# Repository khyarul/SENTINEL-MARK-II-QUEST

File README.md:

# SENTINEL MARK II (QUEST) - Line Follower Path Planning + Oled I2C User Interface
- Arduino compatible based on Maple Mini board (STM32F103CBT6)
- Burn and update firmware via USB-OTG
- BTS7960 motor driver 2 port + encoder
- OLED I2C SSD1306 128x64
- external eeprom (24LCxxx)
- 2 port for mini servo 5V
- 1 port for extinguisher motor (adjustable voltage using PWM) 
- external serial port (Serial1)

### Schematic (made using Kicad)
available in "Schematic" folder:
- SENTINEL Mark II - Quest.pro (Kicad Project)

### Gerber (3 board):
- Core + Driver motor: [Here](https://www.pcbway.com/project/shareproject/SENTINEL_mark_II__QUEST___Core___motor_driver_.html)
- Button + LCD: [Here](https://www.pcbway.com/project/shareproject/SENTINEL_mark_II__QUEST___button___eeprom___lcd_.html)
- Sensor: [Here](https://www.pcbway.com/project/shareproject/SENTINEL_mark_II__QUEST___Sensor_.html)

### Board Preview

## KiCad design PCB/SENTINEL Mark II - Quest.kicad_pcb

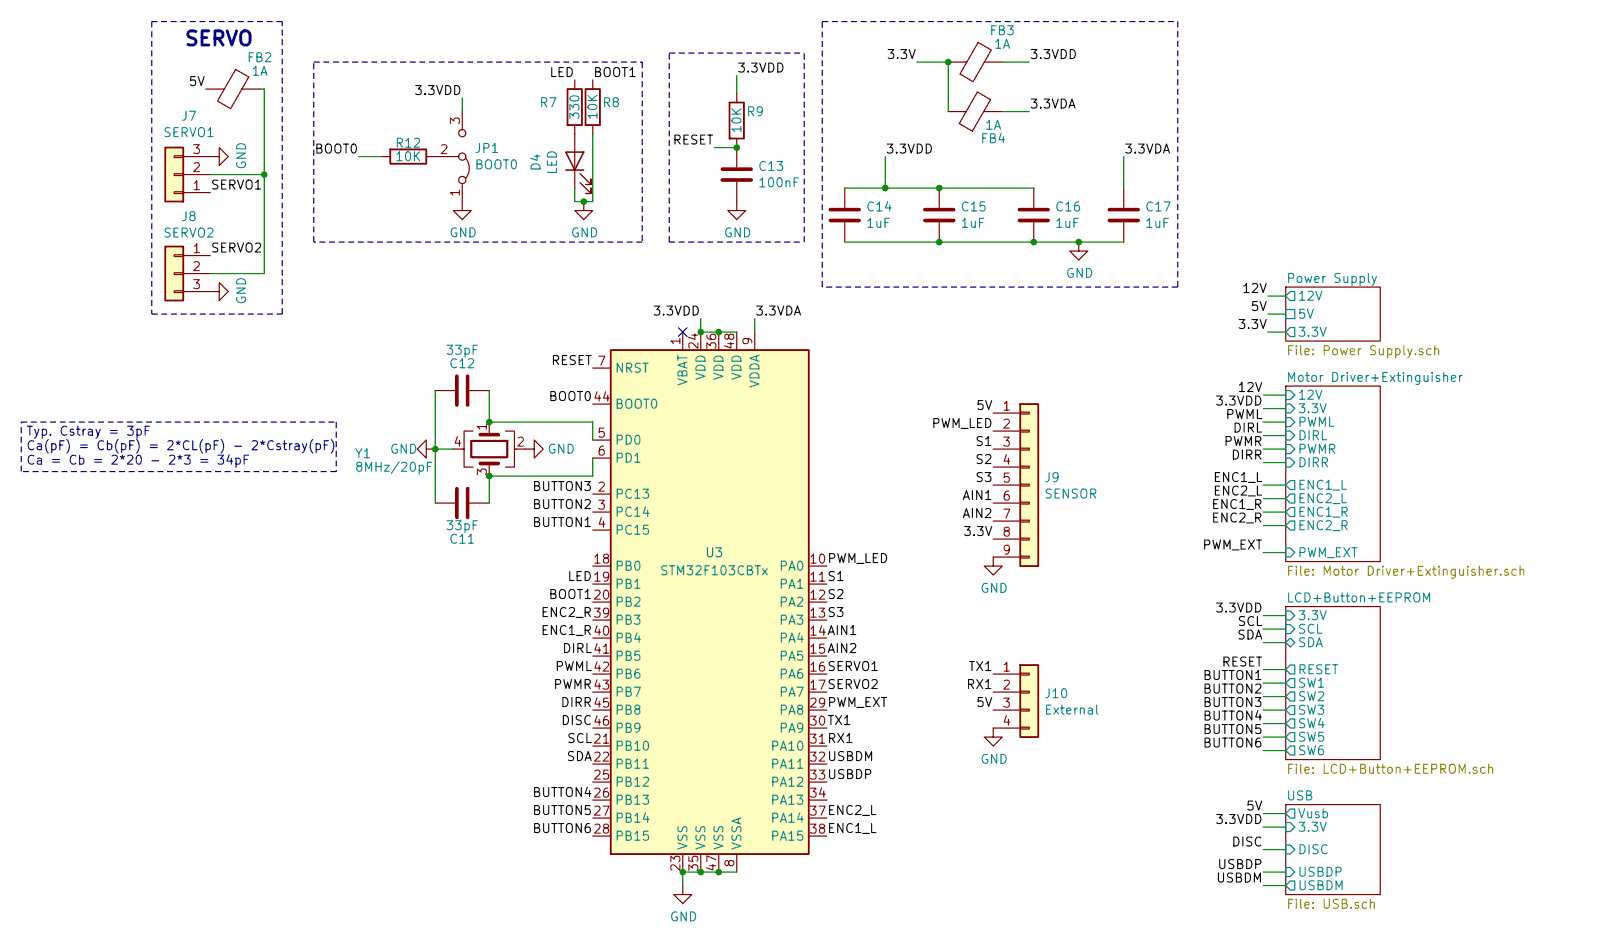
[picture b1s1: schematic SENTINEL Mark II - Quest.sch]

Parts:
C11, C12: 33pF; C_0805_2012Metric
C13: 100nF; C_0805_2012Metric
C14, C15, C16, C17: 1uF; C_0805_2012Metric
D4: LED; LED_0805_2012Metric
FB2, FB3, FB4: 1A; L_0805_2012Metric
J7: SERVO1; PinHeader_1x03_P2.54mm_Vertical
J8: SERVO2; PinHeader_1x03_P2.54mm_Vertical
J9: SENSOR; PinHeader_1x09_P2.54mm_Horizontal
J10: External; PinHeader_1x04_P2.54mm_Vertical
JP1: BOOT0; PinHeader_1x03_P2.54mm_Vertical
R7: 330; R_0805_2012Metric
R8, R9, R12: 10K; R_0805_2012Metric
U3: STM32F103CBTx; LQFP-48_7x7mm_P0.5mm
Y1: 8MHz/20pF; Crystal_SMD_3225-4Pin_3.2x2.5mm_HandSoldering

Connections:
/3.3V: FB3.2, FB4.1, J9.8; also elsewhere on the board
/3.3VDA: C17.1, FB4.2, U3.9 (VDDA)
/5V: FB2.2, J9.1, J10.3; also elsewhere on the board
/AIN1: J9.6, U3.14 (PA4)
/AIN2: J9.7, U3.15 (PA5)
/BOOT0: R12.2, U3.44 (BOOT0)
/BOOT1: R8.1, U3.20 (PB2)
/BUTTON1: U3.4 (PC15); also elsewhere on the board
/BUTTON2: U3.3 (PC14); also elsewhere on the board
/BUTTON3: U3.2 (PC13); also elsewhere on the board
/BUTTON4: U3.26 (PB13); also elsewhere on the board
/BUTTON5: U3.27 (PB14); also elsewhere on the board
/BUTTON6: U3.28 (PB15); also elsewhere on the board
/DIRL: U3.41 (PB5); also elsewhere on the board
/DIRR: U3.45 (PB8); also elsewhere on the board
/DISC: U3.46 (PB9); also elsewhere on the board
/ENC1_L: U3.38 (PA15); also elsewhere on the board
/ENC2_L: U3.37 (PA14); also elsewhere on the board
/LED: R7.1, U3.19 (PB1)
/PWML: U3.42 (PB6); also elsewhere on the board
/PWMR: U3.43 (PB7); also elsewhere on the board
/PWM_EXT: U3.29 (PA8); also elsewhere on the board
/PWM_LED: J9.2, U3.10 (PA0)
/RESET: C13.1, R9.2, U3.7 (NRST); also elsewhere on the board
/RX1: J10.2, U3.31 (PA10)
/S1: J9.3, U3.11 (PA1)
/S2: J9.4, U3.12 (PA2)
/S3: J9.5, U3.13 (PA3)
/SCL: U3.21 (PB10); also elsewhere on the board
/SDA: U3.22 (PB11); also elsewhere on the board
/SERVO1: J7.1, U3.16 (PA6)
/SERVO2: J8.1, U3.17 (PA7)
/TX1: J10.1, U3.30 (PA9)
/USBDM: U3.32 (PA11); also elsewhere on the board
/USBDP: U3.33 (PA12); also elsewhere on the board
unnamed: C11.2, U3.6 (PD1), Y1.3
unnamed: C12.2, U3.5 (PD0), Y1.1
unnamed: D4.2 (A), R7.2
unnamed: FB2.1, J7.2, J8.2
unnamed: JP1.2 (C), R12.1

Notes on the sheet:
Typ. Cstray = 3pF Ca(pF) = Cb(pF) = 2*CL(pF) - 2*Cstray(pF) Ca = Cb = 2*20 - 2*3 = 34pF
SERVO

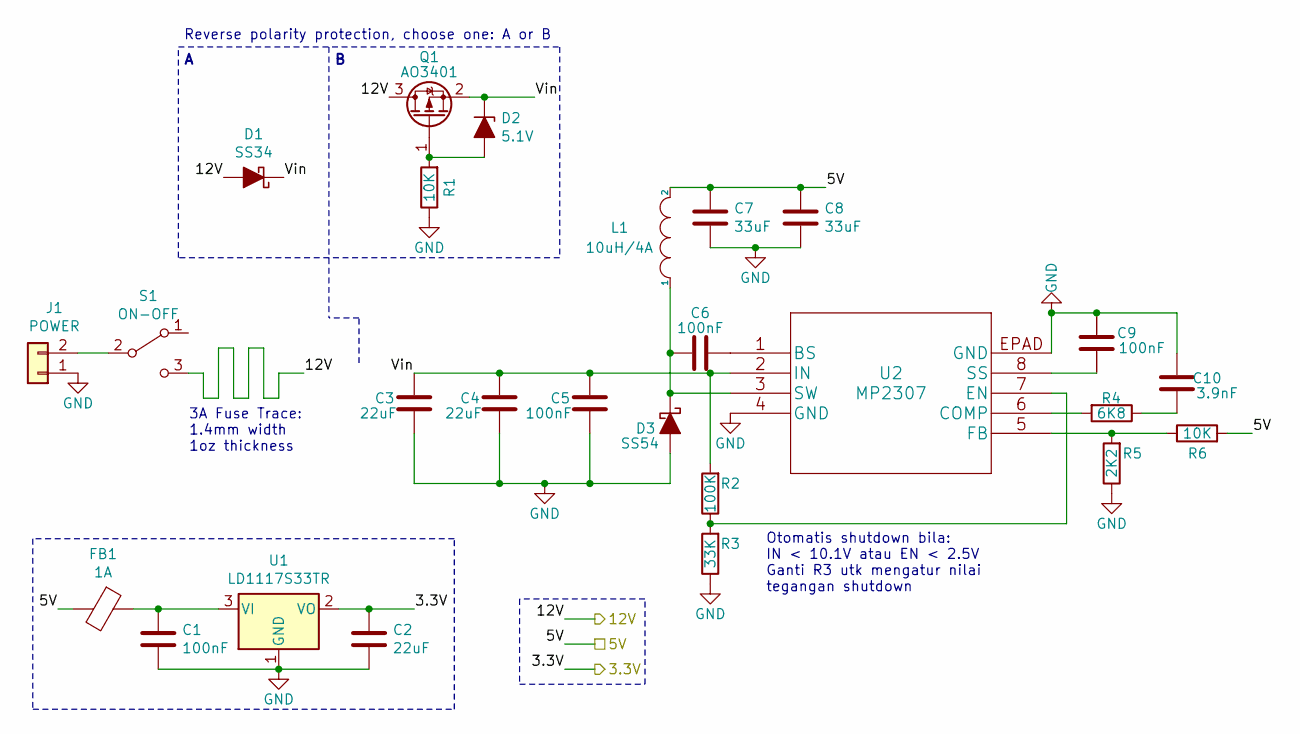
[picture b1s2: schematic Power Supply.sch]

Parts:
C1, C5, C6, C9: 100nF; C_0805_2012Metric
C2, C3, C4: 22uF; C_0805_2012Metric
C7, C8: 33uF; C_0805_2012Metric
C10: 3.9nF; C_0805_2012Metric
D1: SS34; D_SMA
D2: 5.1V; D_SOD-123
D3: SS54; D_SMA
FB1: 1A; L_0805_2012Metric
J1: POWER; PinHeader_1x02_P2.54mm_Vertical
L1: 10uH/4A; L_7.3x7.3_H3.5
Q1: AO3401; SOT-23
R1, R6: 10K; R_0805_2012Metric
R2: 100K; R_0805_2012Metric
R3: 33K; R_0805_2012Metric
R4: 6K8; R_0805_2012Metric
R5: 2K2; R_0805_2012Metric
S1: ON-OFF; switch_slide_2.54
U1: LD1117S33TR; SOT-223-3_TabPin2
U2: MP2307

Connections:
/3.3V: C2.1, U1.2 (VO); also elsewhere on the board
/5V: C7.1, C8.1, FB1.2, L1.2, R6.2; also elsewhere on the board
/12V: D1.2 (A), Q1.3 (D), S1.3 (C); also elsewhere on the board
/Power Supply/Vin: C3.1, C4.1, C5.1, D1.1 (K), D2.1 (K), Q1.2 (S), R2.2, U2.2 (IN)
unnamed: C1.1, FB1.1, U1.3 (VI)
unnamed: C6.1, U2.1 (BS)
unnamed: C6.2, D3.1 (K), L1.1, U2.3 (SW)
unnamed: C9.1, U2.8 (SS)
unnamed: C10.1, R4.1
unnamed: D2.2 (A), Q1.1 (G), R1.2
unnamed: J1.2, S1.2 (B)
unnamed: R2.1, R3.2, U2.7 (EN)
unnamed: R4.2, U2.6 (COMP)
unnamed: R5.2, R6.1, U2.5 (FB)

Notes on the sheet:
Otomatis shutdown bila: IN < 10.1V atau EN < 2.5V Ganti R3 utk mengatur nilai tegangan shutdown
3A Fuse Trace: 1.4mm width 1oz thickness
Reverse polarity protection, choose one: A or B

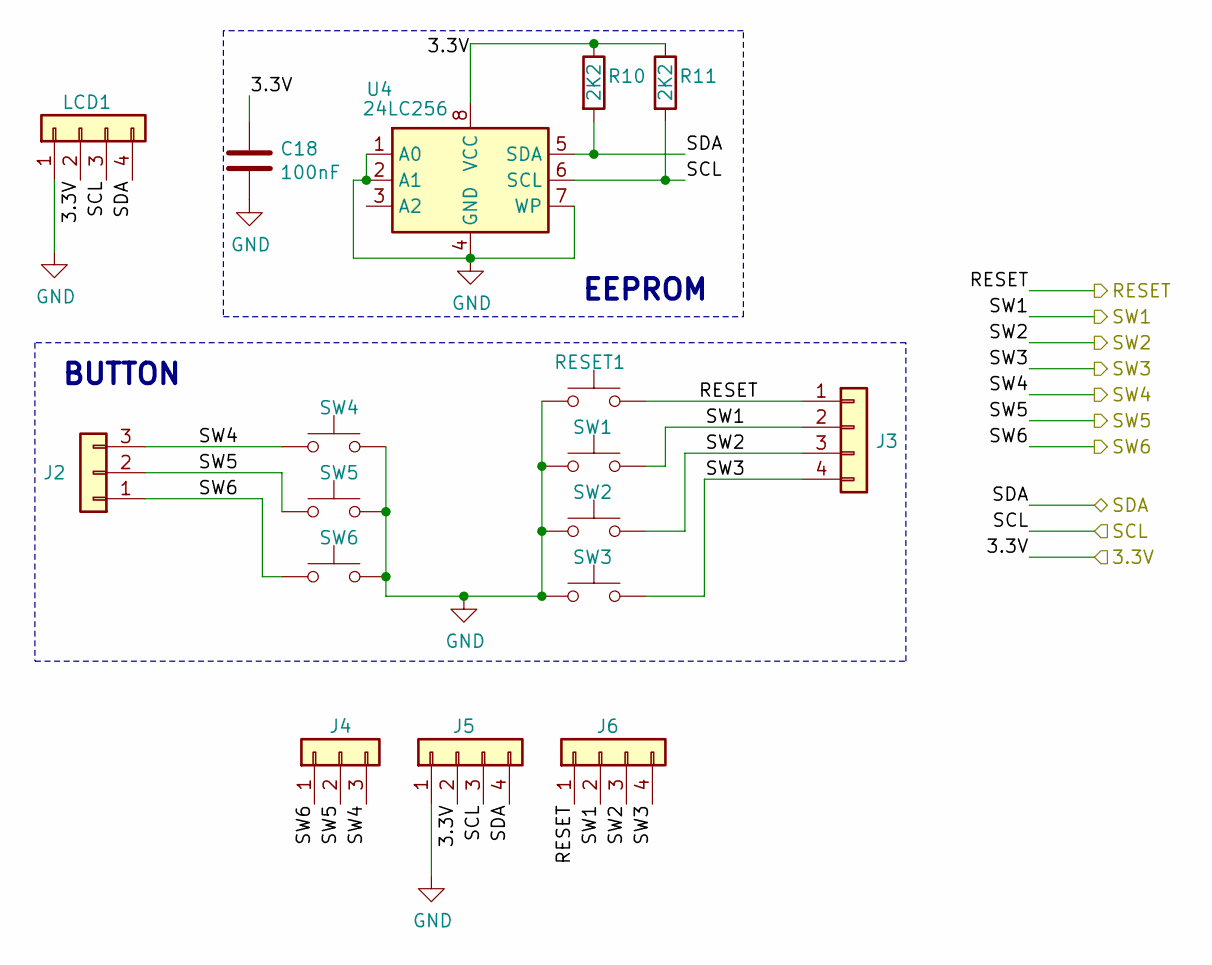
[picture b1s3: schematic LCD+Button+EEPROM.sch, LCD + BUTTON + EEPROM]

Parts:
C18: 100nF; C_0805_2012Metric
J2, J4: Conn_01x03; PinHeader_1x03_P2.54mm_Vertical
J3, J5, J6: Conn_01x04; PinHeader_1x04_P2.54mm_Vertical
LCD1: LCD; OLED_I2C_128x64
R10, R11: 2K2; R_0805_2012Metric
RESET1: RESET; Push_button_silicon_mute
SW1: B1; Push_button_silicon_mute
SW2: B2; Push_button_silicon_mute
SW3: B3; Push_button_silicon_mute
SW4: B4; Push_button_silicon_mute
SW5: B5; Push_button_silicon_mute
SW6: B6; Push_button_silicon_mute
U4: 24LC256; SO-8_3.9x4.9mm_P1.27mm

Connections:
/BUTTON1: J3.2, J6.2, SW1.2; also elsewhere on the board
/BUTTON2: J3.3, J6.3, SW2.2; also elsewhere on the board
/BUTTON3: J3.4, J6.4, SW3.2; also elsewhere on the board
/BUTTON4: J2.3, J4.3, SW4.1; also elsewhere on the board
/BUTTON5: J2.2, J4.2, SW5.1; also elsewhere on the board
/BUTTON6: J2.1, J4.1, SW6.1; also elsewhere on the board
/RESET: J3.1, J6.1, RESET1.2; also elsewhere on the board
/SCL: J5.3, LCD1.3, R11.2, U4.6 (SCL); also elsewhere on the board
/SDA: J5.4, LCD1.4, R10.2, U4.5 (SDA); also elsewhere on the board

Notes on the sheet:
EEPROM
BUTTON

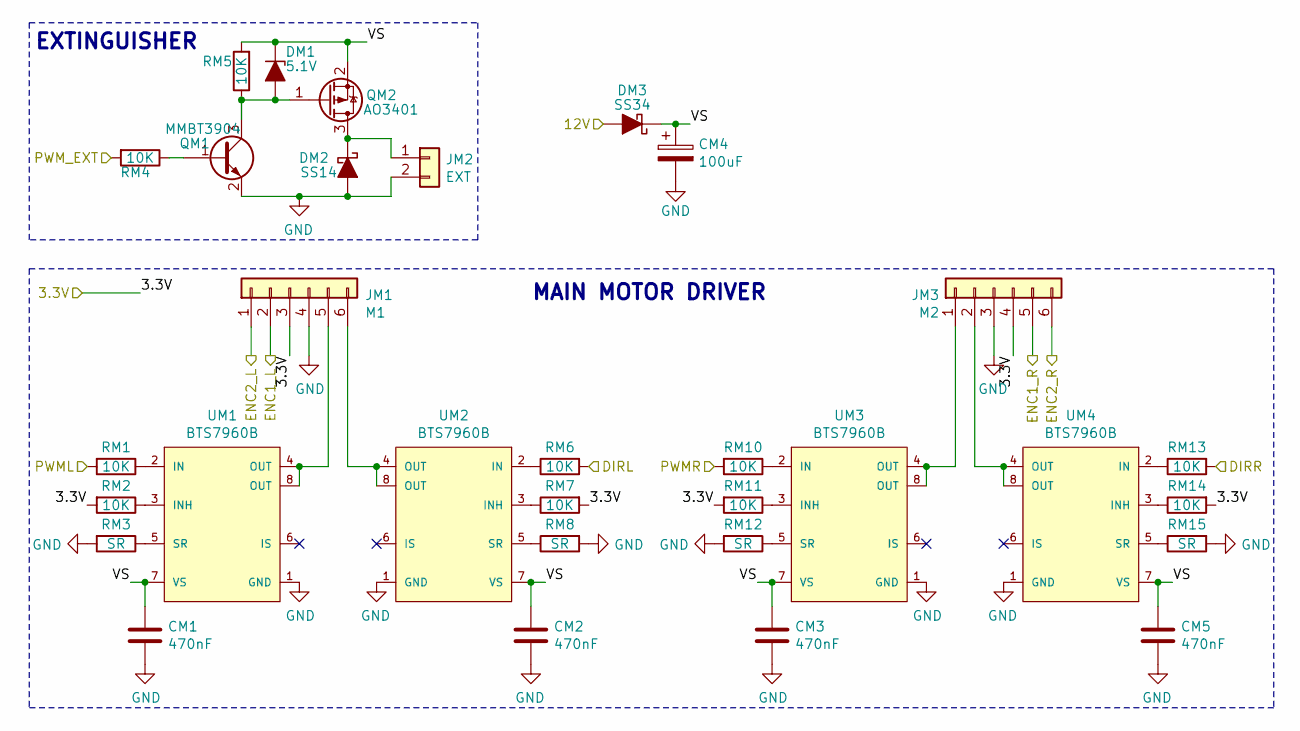
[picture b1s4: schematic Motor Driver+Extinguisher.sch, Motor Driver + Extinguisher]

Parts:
CM1, CM2, CM3, CM5: 470nF; C_0805_2012Metric
CM4: 100uF; CP_Elec_6.3x7.7
DM1: 5.1V; D_SOD-123
DM2: SS14; D_SMA
DM3: SS34; D_SMA
JM1: M1; JST_PH_S6B-PH-K_1x06_P2.00mm_Horizontal
JM2: EXT; PinHeader_1x02_P2.54mm_Vertical
JM3: M2; JST_PH_S6B-PH-K_1x06_P2.00mm_Horizontal
QM1: MMBT3904; SOT-23
QM2: AO3401; SOT-23
RM1, RM2, RM4, RM5, RM6, RM7, RM10, RM11, RM13, RM14: 10K; R_0805_2012Metric
RM3, RM8, RM12, RM15: SR; R_0805_2012Metric
UM1, UM2, UM3, UM4: BTS7960B; Infineon-BTS7960B-Level_A

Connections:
/12V: DM3.2 (A); also elsewhere on the board
/DIRL: RM6.2; also elsewhere on the board
/DIRR: RM13.2; also elsewhere on the board
/ENC1_L: JM1.2; also elsewhere on the board
/ENC2_L: JM1.1; also elsewhere on the board
/Motor Driver+Extinguisher/VS: CM1.1, CM2.1, CM3.1, CM4.1, CM5.1, DM1.1 (K), DM3.1 (K), QM2.2 (S), RM5.2, UM1.7 (VS), UM2.7 (VS), UM3.7 (VS), UM4.7 (VS); also elsewhere on the board
/PWML: RM1.2; also elsewhere on the board
/PWMR: RM10.2; also elsewhere on the board
/PWM_EXT: RM4.2; also elsewhere on the board
unnamed: DM1.2 (A), QM1.3 (C), QM2.1 (G), RM5.1
unnamed: DM2.1 (K), JM2.1, QM2.3 (D)
unnamed: JM1.5, UM1.4 (OUT), UM1.8 (OUT)
unnamed: JM1.6, UM2.4 (OUT), UM2.8 (OUT)
unnamed: QM1.1 (B), RM4.1
unnamed: RM1.1, UM1.2 (IN)
unnamed: RM2.1, UM1.3 (INH)
unnamed: RM3.1, UM1.5 (SR)
unnamed: RM6.1, UM2.2 (IN)
unnamed: RM7.1, UM2.3 (INH)
unnamed: RM8.1, UM2.5 (SR)
unnamed: RM10.1, UM3.2 (IN)
unnamed: RM11.1, UM3.3 (INH)
unnamed: RM12.1, UM3.5 (SR)
unnamed: RM13.1, UM4.2 (IN)
unnamed: RM14.1, UM4.3 (INH)
unnamed: RM15.1, UM4.5 (SR)

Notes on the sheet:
MAIN MOTOR DRIVER
EXTINGUISHER

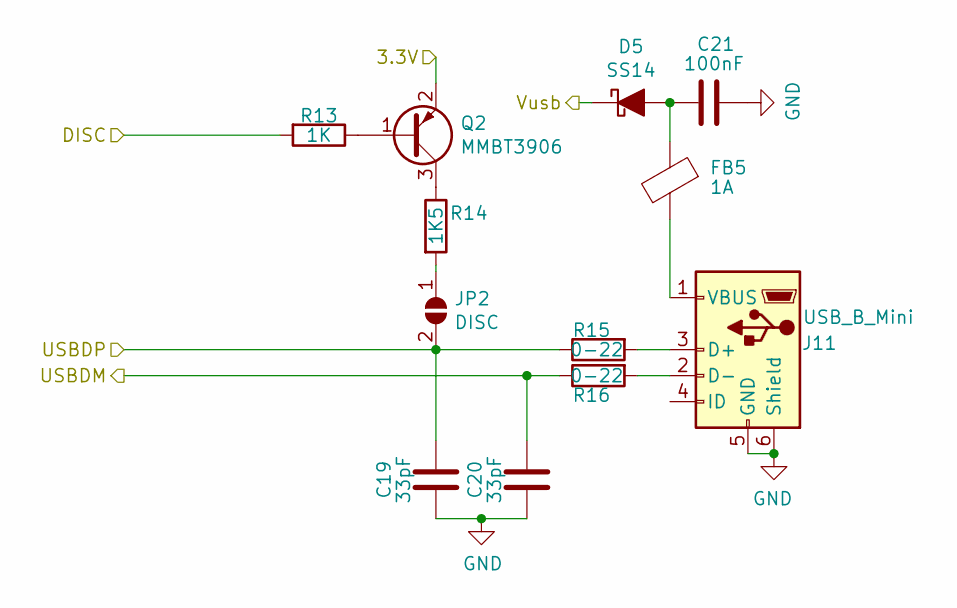
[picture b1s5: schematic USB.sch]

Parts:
C19, C20: 33pF
C21: 100nF
D5: SS14
FB5: 1A
J11: USB_B_Mini
JP2: DISC
Q2: MMBT3906; SOT-23
R13: 1K
R14: 1K5
R15, R16: 0-22

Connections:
/5V: D5.1 (K); also elsewhere on the board
/DISC: R13.2; also elsewhere on the board
/USBDM: C20.1, R16.1; also elsewhere on the board
/USBDP: C19.1, JP2.2 (B), R15.1; also elsewhere on the board
unnamed: C21.2, D5.2 (A), FB5.1
unnamed: FB5.2, J11.1 (VBUS)
unnamed: J11.2 (D-), R16.2
unnamed: J11.3 (D+), R15.2
unnamed: JP2.1 (A), R14.2
unnamed: Q2.1 (B), R13.1
unnamed: Q2.3 (C), R14.1

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
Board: 2 copper layers, 111 parts (0 on the bottom side), 84 nets, no tracks yet.

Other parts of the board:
DM4: 5.1V; D_SOD-123
QM3: AO3401; SOT-23
RM9: 10K; R_0805_2012Metric

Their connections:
/12V: QM3.3; also elsewhere on the board
/Motor Driver+Extinguisher/VS: DM4.1, QM3.2; also elsewhere on the board
unnamed: DM4.2, QM3.1, RM9.2

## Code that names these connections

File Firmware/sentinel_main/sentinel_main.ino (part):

/*
  UP    : PB15
  DOWN  : PB14
  +     : PC15
  -     : PC14
  Enter : PB13
  Back  : PC13

  SDA   : PB11
  SCL   : PB10
  Tx1   : PA9
  Rx1   : PA10

  LED   : PB1
  Batt  : PB0
  LED_sensor  : PA0
  S1    : PA1
  S2    : PA2
  S3    : PA3
  AIN1  : PA4
  AIN2  : PA5

  DIRL  : PB5
  PWML  : PB6
  PWMR  : PB7
  DIRR  : PB8

  ENC1_R: PB4
  ENC2_R: PB3
  ENC1_L: PA15
  ENC2_L: PA14

  SERVO1: PA6
  SERVO2: PA7
  Ext   : PA8
*/

#include <Wire.h>
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}

//Button
#define OK digitalRead(PB13)
#define UP digitalRead(PB15)
#define DOWN digitalRead(PB14)
#define BACK digitalRead(PC13)
#define PLUS digitalRead(PC15)
#define MIN digitalRead(PC14)

//Motor Driver
//HardwareTimer timer(1);
#define pwmL PB6
#define pwmR PB7
#define dirL PB5
#define dirR PB8
//int16_t speedL = 0, speedR = 0;
int16_t error = 0, lastError = 0;
uint32_t lastTime = 0;
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//Sensor
#define led_ON digitalWrite(led, 1)
#define led_OFF digitalWrite(led, 0)
#define led PA0
#define sensorL PA5
#define sensorR PA4
#define A PA1
#define B PA2
#define C PA3
//uint8_t pinSensor[3] = {PA5, PA4, PB0};
uint16_t arraySensor[14], adcSensor[3];
int8_t sensor_logic = 0;
uint16_t bitSensor = 0;
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  initSensor();
  switchSensor(0);

  Wire.setSDA(PB11);
  Wire.setSCL(PB10);
  lcd.begin();
  lcd.setPowerSave(0);
  lcd.setFlipMode(1);
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      lcd.clear();
    }
  }
  servoR.attach(PA6);
  servoL.attach(PA7);
  servoR.write(ee.SV1[0]);
  servoL.write(ee.SV2[0]);
  lcd.clear();
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
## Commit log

2020-09-19 KICAD schematic
2020-09-19 Footprint Assigned
2020-09-20 Add new file
    edge-cut.cdr
2020-09-20 PCB Edge-cute line
    PCB Edge-cute line/milling/outer line
2020-09-22 PCB Edge-cut
2020-09-22 KICAD
2020-09-27 Circuit fix (Kicad)
2020-10-01 Gerber File
2020-10-01 Schematic
2020-10-01 gerber button + lcd
2020-10-01 sensor Schematic added
2020-10-01 Gerber moved to PCBway
2020-10-01 Added sensor schematic
2020-10-03 Schematic Kicad
    + voltage divider (for battery sensor)
2020-10-13 BOM/Part list
2020-10-23 Part list
2020-10-23 Schematic update
2021-09-26 Firmware
    The reading of the sensor error value is already using "Mean Error" algorithm
    No longer using manual method "switch case"
    -------------------------------------------------------------------------------------
    Pembacaan nilai error sensor sudah menggunakan algoritma "Mean Error"
    Tidak lagi menggunakan metode manual "switch case"
2021-09-26 Firmware
    perbaikan mode ubah warna BLK atau WHT saat robot eksekusi plan
